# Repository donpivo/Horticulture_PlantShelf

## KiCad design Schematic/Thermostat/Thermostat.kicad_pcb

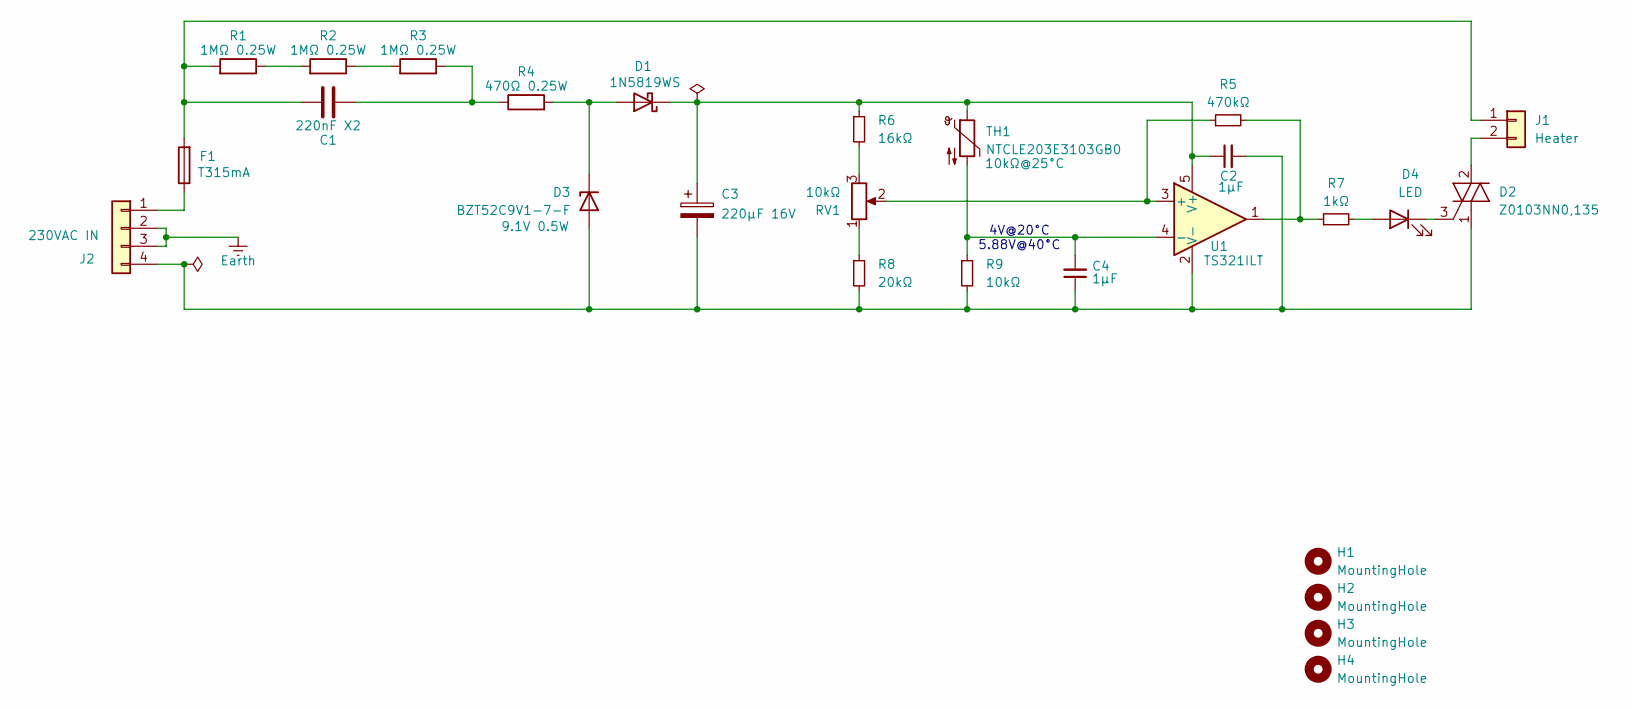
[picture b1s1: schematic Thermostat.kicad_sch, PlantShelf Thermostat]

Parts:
C1: 220nF X2; C_Rect_L18.0mm_W8.0mm_P15.00mm_FKS3_FKP3
C2, C4: 1µF; C_0603_1608Metric_Pad1.08x0.95mm_HandSolder
C3: 220µF 16V; CP_Elec_6.3x7.7
D1: 1N5819WS; D_SOD-123
D2: Z0103NN0,135; SOT-223
D3: BZT52C9V1-7-F; D_SOD-123
D4: LED; LED_D3.0mm_Horizontal_O1.27mm_Z2.0mm
F1: T315mA; Fuse_Littelfuse_372_D8.50mm
H1, H2, H3, H4: MountingHole; MountingHole_3.2mm_M3
J1: Heater; ScrewTerminal_DB128L-5.08-2P-BK-S
J2: 230VAC IN; Pluggable_DB2ERC-5.08-4P-BK
R1, R2, R3: 1MΩ 0.25W; R_1206_3216Metric_Pad1.30x1.75mm_HandSolder
R4: 470Ω 0.25W; R_1206_3216Metric_Pad1.30x1.75mm_HandSolder
R5: 470kΩ; R_0603_1608Metric_Pad0.98x0.95mm_HandSolder
R6: 16kΩ; R_0603_1608Metric_Pad0.98x0.95mm_HandSolder
R7: 1kΩ; R_0603_1608Metric_Pad0.98x0.95mm_HandSolder
R8: 20kΩ; R_0603_1608Metric_Pad0.98x0.95mm_HandSolder
R9: 10kΩ; R_0603_1608Metric_Pad0.98x0.95mm_HandSolder
RV1: 10kΩ; Potentiometer_Bourns_PTV09A-2_Single_Horizontal
TH1: NTCLE203E3103GB0; NTCLE203E3103FB0A
U1: TS321ILT; SOT-23-5

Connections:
Earth: J2.2, J2.3
unnamed: C1.1, R3.1, R4.1
unnamed: D1.2 (A), D3.1 (K), R4.2
unnamed: C2.1, C3.1, D1.1 (K), R6.1, TH1.1, U1.5 (V+)
unnamed: D2.3 (G), D4.1 (K)
unnamed: C2.2, C3.2, C4.1, D2.1 (T1), D3.2 (A), J2.4, R8.2, R9.2, U1.2 (V-)
unnamed: D4.2 (A), R7.2
unnamed: C1.2, F1.2, J1.1, R1.2
unnamed: D2.2 (T2), D2.4 (T2), J1.2
unnamed: F1.1, J2.1
unnamed: R1.1, R2.2
unnamed: R2.1, R3.2
unnamed: R5.2, R7.1, U1.1
unnamed: R6.2, RV1.3
unnamed: R8.1, RV1.1
unnamed: R5.1, RV1.2, U1.3 (+)
unnamed: C4.2, R9.1, TH1.2, U1.4 (-)

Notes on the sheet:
4V@20°C 5.88V@40°C

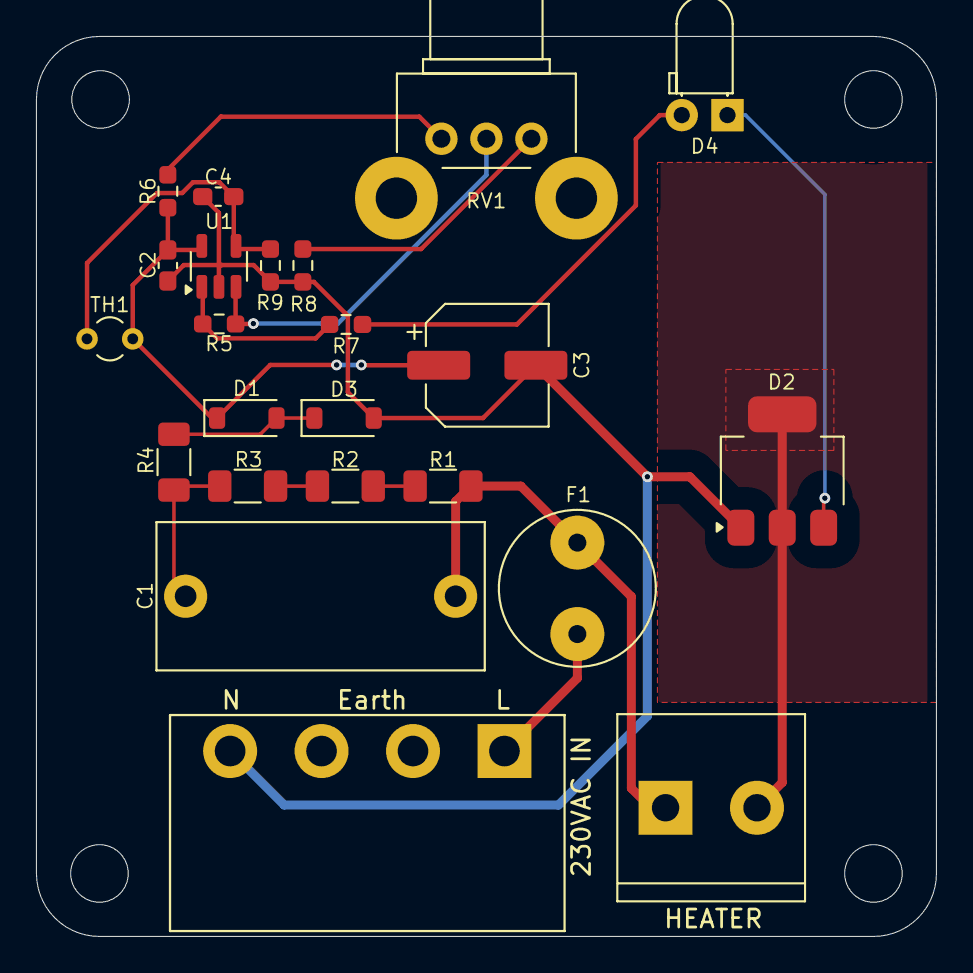
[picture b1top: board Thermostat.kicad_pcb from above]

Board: 2 copper layers, 50.0 x 50.0 mm, 27 parts (0 on the bottom side), 17 nets.

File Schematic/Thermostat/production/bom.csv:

Designator,Footprint,Quantity,Value,LCSC Part #
C1,C_Rect_L18.0mm_W8.0mm_P15.00mm_FKS3_FKP3,1,220nF X2,
"C2, C4",0603,2,1µF,
C3,CP_Elec_6.3x7.7,1,220µF 16V,
D1,D_SOD-123,1,1N5819WS,
D2,SOT-223,1,"Triac_Z0103NN0,135",
D3,D_SOD-123,1,BZT52C9V1-7-F,
D4,LED_D3.0mm_Horizontal_O1.27mm_Z2.0mm,1,LED,
F1,Fuse_Littelfuse_372_D8.50mm,1,T315mA,
J1,ScrewTerminal_DB128L-5.08-2P-BK-S,1,Heater,
J2,Pluggable_DB2ERC-5.08-4P-BK,1,230VAC IN,
"R1, R2, R3",1206,3,1MΩ 0.25W,
R4,1206,1,470Ω 0.25W,
R5,0603,1,1MΩ,
R6,0603,1,27kΩ,
R7,0603,1,1kΩ,
R8,0603,1,47kΩ,
R9,0603,1,10kΩ,
RV1,Potentiometer_Bourns_PTV09A-2_Single_Horizontal,1,20kΩ,
TH1,NTCLE203E3103FB0A,1,NTCLE203E3103GB0,
U1,SOT-23-5,1,TS321ILT,

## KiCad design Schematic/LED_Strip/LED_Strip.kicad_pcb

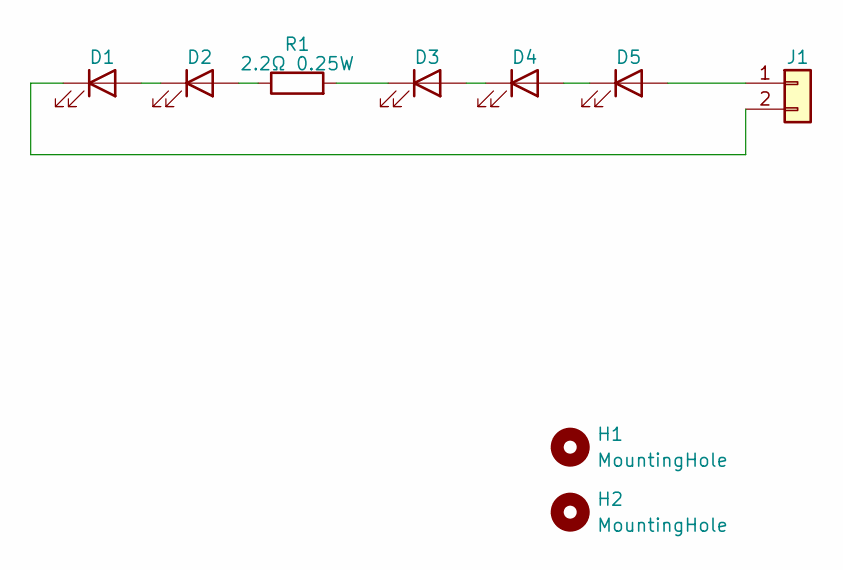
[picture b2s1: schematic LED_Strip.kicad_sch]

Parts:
D1, D2, D3, D4, D5: GW QSLMS2.HM-H8H9-XX52-1U1V; GW_QSLMS2.HM-H8H9-XX53-1U1V
H1, H2: MountingHole; MountingHole_3.2mm_M3
J1: Pads_Dual_3x4
R1: 2.2Ω 0.25W; R_1206_3216Metric_Pad1.30x1.75mm_HandSolder

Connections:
unnamed: D1.2 (A), D2.1 (K)
unnamed: D1.1 (K), J1.2
unnamed: D2.2 (A), R1.1
unnamed: D3.2 (A), D4.1 (K)
unnamed: D3.1 (K), R1.2
unnamed: D4.2 (A), D5.1 (K)
unnamed: D5.2 (A), J1.1

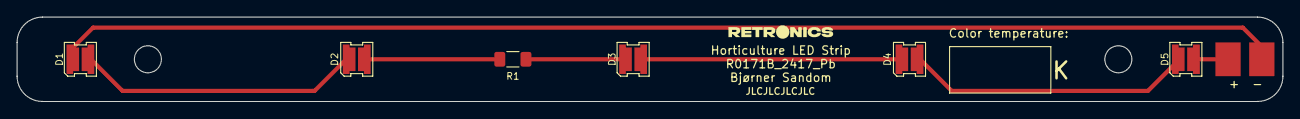
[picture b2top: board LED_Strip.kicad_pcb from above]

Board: 2 copper layers, 150.0 x 10.0 mm, 9 parts (0 on the bottom side), 7 nets.

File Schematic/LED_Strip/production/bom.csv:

Designator,Footprint,Quantity,Value,LCSC Part #
"D1, D2, D3, D4, D5",GW_QSLMS2.HM-H8H9-XX53-1U1V,5,GW QSLMS2.HM-H8H9-XX52-1U1V,
"H1, H2",MountingHole_3.2mm_M3,2,MountingHole,
J1,Pads_Dual_3x4,1,~,
R1,1206,1,2.2Ω 0.25W,

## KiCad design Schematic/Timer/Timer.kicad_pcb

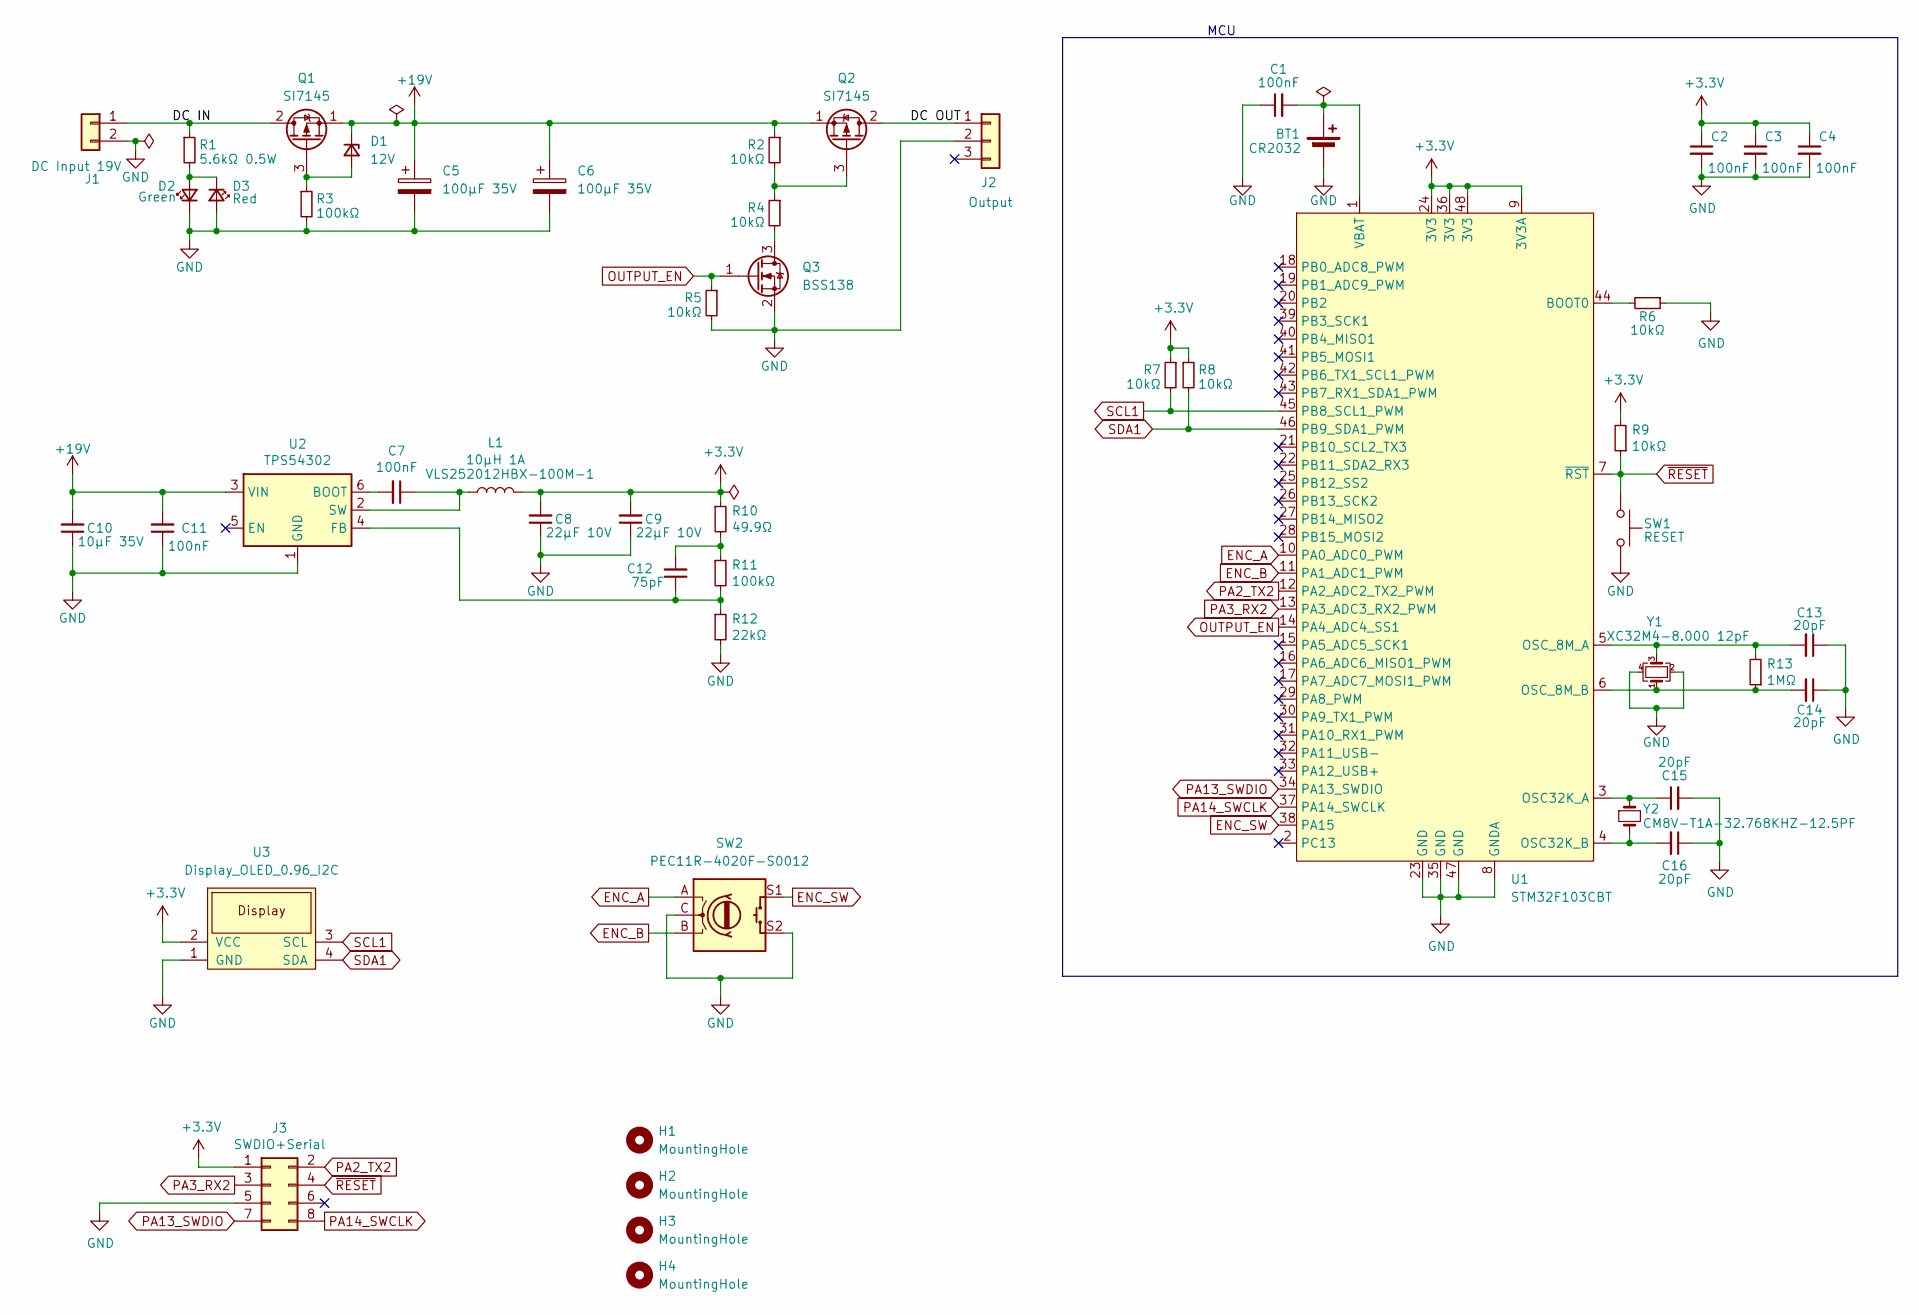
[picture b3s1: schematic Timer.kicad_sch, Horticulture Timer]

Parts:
BT1: CR2032; BS7
C1, C2, C3, C4, C7, C11: 100nF; C_0603_1608Metric_Pad1.08x0.95mm_HandSolder
C5, C6: 100µF 35V; CP_Elec_6.3x7.7
C8, C9: 22µF 10V; C_0603_1608Metric_Pad1.08x0.95mm_HandSolder
C10: 10µF 35V; C_0603_1608Metric_Pad1.08x0.95mm_HandSolder
C12: 75pF; C_0603_1608Metric_Pad1.08x0.95mm_HandSolder
C13, C14, C15, C16: 20pF; C_0603_1608Metric_Pad1.08x0.95mm_HandSolder
D1: 12V; D_SOD-123
D2: Green; LED_0805_2012Metric_Pad1.15x1.40mm_HandSolder
D3: Red; LED_0805_2012Metric_Pad1.15x1.40mm_HandSolder
H1, H2, H3, H4: MountingHole; MountingHole_3.2mm_M3
J1: DC Input 19V; Pluggable_DB2ERC-5.08-2P-BK
J2: Output; Pluggable_DB2ERC-5.08-3P-BK
J3: SWDIO+Serial; IDC-Header_2x04_P2.54mm_Vertical
L1: 10µH 1A; L_Taiyo-Yuden_NR-20xx_HandSoldering
Q1, Q2: SI7145; SON8_SI7135DP-T1-GE3_VIS
Q3: BSS138; SOT-23
R1: 5.6kΩ 0.5W; R_1210_3225Metric_Pad1.30x2.65mm_HandSolder
R2, R4, R5, R6, R7, R8, R9: 10kΩ; R_0603_1608Metric_Pad0.98x0.95mm_HandSolder
R3, R11: 100kΩ; R_0603_1608Metric_Pad0.98x0.95mm_HandSolder
R10: 49.9Ω; R_0603_1608Metric_Pad0.98x0.95mm_HandSolder
R12: 22kΩ; R_0603_1608Metric_Pad0.98x0.95mm_HandSolder
R13: 1MΩ; R_0603_1608Metric_Pad0.98x0.95mm_HandSolder
SW1: RESET; SKTHACE010
SW2: PEC11R-4020F-S0012
U1: STM32F103CBT; LQFP-48_7x7mm_P0.5mm
U2: TPS54302; SOT-23-6_Handsoldering
U3: Display_OLED_0.96_I2C; Display_OLED_0.96in_I2C
Y1: XC32M4-8.000 12pF; Crystal_SMD_3225-4Pin_3.2x2.5mm
Y2: CM8V-T1A-32.768KHZ-12.5PF; Crystal_SMD_MicroCrystal_CC8V-T1A-2Pin_2.0x1.2mm_HandSolder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

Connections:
+3.3V: C2.1, C3.1, C4.1, C8.2, C9.2, J3.1, L1.2, R7.1, R8.1, R9.2, R10.1, U1.9 (3V3A), U1.24 (3V3), U1.36 (3V3), U1.48 (3V3), U3.2 (VCC)
+19V: C5.1, C6.1, C10.2, C11.2, D1.1 (K), Q1.1 (S), Q2.1 (S), R2.1, U2.3 (VIN)
/DC IN: J1.1, Q1.2 (D), R1.1
/DC OUT: J2.1, Q2.2 (D)
ENC_A: SW2.A, U1.10 (PA0_ADC0_PWM)
ENC_B: SW2.B, U1.11 (PA1_ADC1_PWM)
ENC_SW: SW2.S1, U1.38 (PA15)
GND: BT1.2 (-), C1.1, C2.2, C3.2, C4.2, C5.2, C6.2, C8.1, C9.1, C10.1, C11.1, C13.1, C14.1, C15.2, C16.1, D2.1 (K), D3.2 (A), J1.2, J2.2, J3.5, Q3.2 (S), R3.2, R5.2, R6.1, R12.2, SW1.2, SW2.C, SW2.S2, U1.8 (GNDA), U1.23 (GND), U1.35 (GND), U1.47 (GND), U2.1 (GND), U3.1 (GND), Y1.2, Y1.4
unnamed: BT1.1 (+), C1.2, U1.1 (VBAT)
unnamed: C12.2, R10.2, R11.1
unnamed: D1.2 (A), Q1.3 (G), R3.1
unnamed: D2.2 (A), D3.1 (K), R1.2
unnamed: Q2.3 (G), R2.2, R4.1
unnamed: Q3.3 (D), R4.2
unnamed: R6.2, U1.44 (BOOT0)
unnamed: C15.1, U1.3 (OSC32K_A), Y2.1
unnamed: C16.2, U1.4 (OSC32K_B), Y2.2
unnamed: C13.2, R13.2, U1.5 (OSC_8M_A), Y1.3
unnamed: C14.2, R13.1, U1.6 (OSC_8M_B), Y1.1
unnamed: C7.2, U2.6 (BOOT)
unnamed: C12.1, R11.2, R12.1, U2.4 (FB)
unnamed: C7.1, L1.1, U2.2 (SW)
OUTPUT_EN: Q3.1 (G), R5.1, U1.14 (PA4_ADC4_SS1)
PA2_TX2: J3.2, U1.12 (PA2_ADC2_TX2_PWM)
PA3_RX2: J3.3, U1.13 (PA3_ADC3_RX2_PWM)
PA13_SWDIO: J3.7, U1.34 (PA13_SWDIO)
PA14_SWCLK: J3.8, U1.37 (PA14_SWCLK)
SCL1: R7.2, U1.45 (PB8_SCL1_PWM), U3.3 (SCL)
SDA1: R8.2, U1.46 (PB9_SDA1_PWM), U3.4 (SDA)
~RESET: J3.4, R9.1, SW1.1, U1.7 (~RST)

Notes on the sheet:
MCU

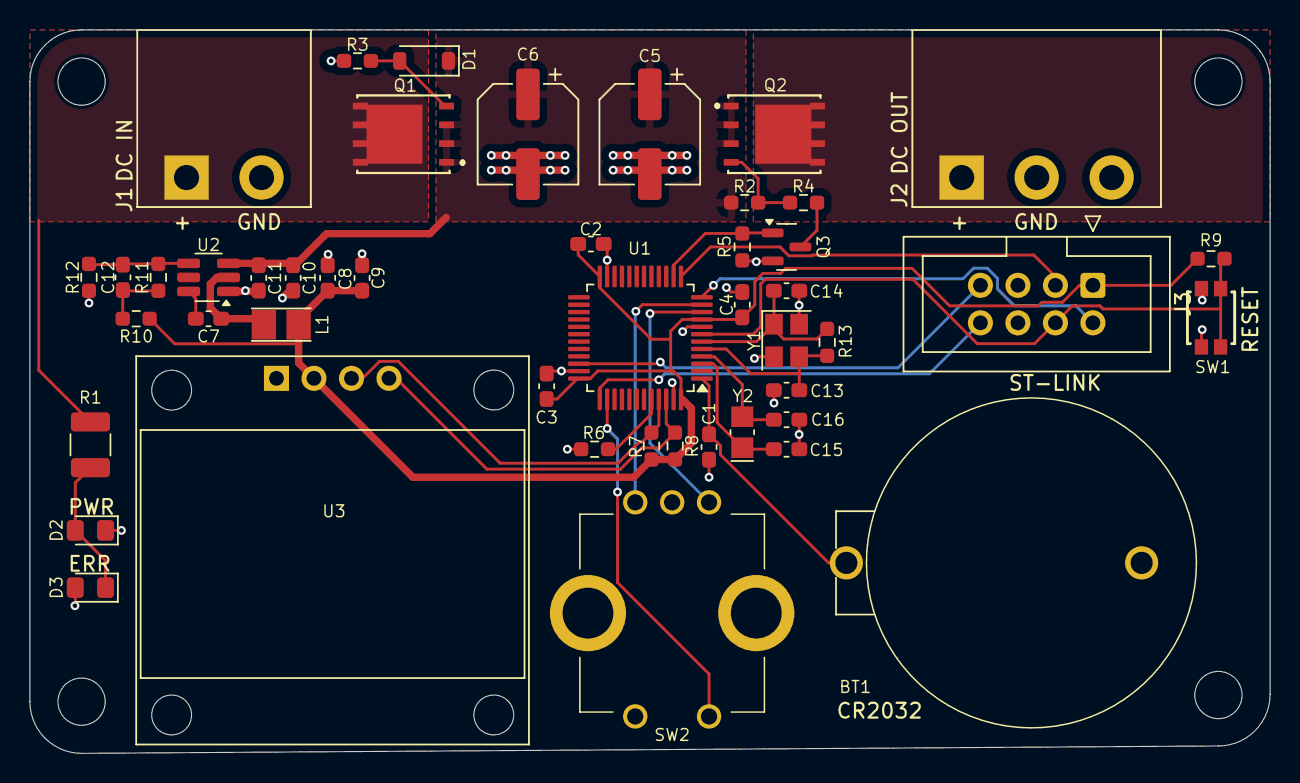
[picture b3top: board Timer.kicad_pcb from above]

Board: 2 copper layers, 84.0 x 49.0 mm, 51 parts (0 on the bottom side), 30 nets.

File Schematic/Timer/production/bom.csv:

Designator,Footprint,Quantity,Value,LCSC Part #
BT1,BS7,1,CR2032,
"C1, C11, C2, C3, C4, C7",0603,6,100nF,
C10,0603,1,10µF 35V,
C12,0603,1,75pF,
"C13, C14, C15, C16",0603,4,20pF,
"C5, C6",CP_Elec_6.3x7.7,2,100µF 35V,
"C8, C9",0603,2,22µF 10V,
D1,D_SOD-123,1,12V,
D2,0805,1,Green,
D3,0805,1,Red,
J1,Pluggable_DB2ERC-5.08-2P-BK,1,DC Input 19V,
J2,Pluggable_DB2ERC-5.08-3P-BK,1,Output,
J3,IDC-Header_2x04_P2.54mm_Vertical,1,SWDIO+Serial,
L1,L_Taiyo-Yuden_NR-20xx_HandSoldering,1,10µH 1A,
"Q1, Q2",SON8_SI7135DP-T1-GE3_VIS,2,SI7145,
Q3,SOT-23,1,BSS138,
R1,1210,1,5.6kΩ 0.5W,
R10,0603,1,49.9Ω,
"R11, R3",0603,2,100kΩ,
R12,0603,1,22kΩ,
R13,0603,1,1MΩ,
"R2, R4, R5, R6, R7, R8, R9",0603,7,10kΩ,
SW1,SKTHACE010,1,RESET,
SW2,PEC11R-4020F-S0012,1,PEC11R-4020F-S0012,
U1,LQFP-48_7x7mm_P0.5mm,1,STM32F103CBT,
U2,SOT-23-6_Handsoldering,1,TPS54302,
U3,Display_OLED_0.96in_I2C,1,Display_OLED_0.96_I2C,
Y1,Crystal_SMD_3225-4Pin_3.2x2.5mm,1,XC32M4-8.000 12pF,
Y2,Crystal_SMD_MicroCrystal_CC8V-T1A-2Pin_2.0x1.2mm_HandSoldering,1,CM8V-T1A-32.768KHZ-12.5PF,

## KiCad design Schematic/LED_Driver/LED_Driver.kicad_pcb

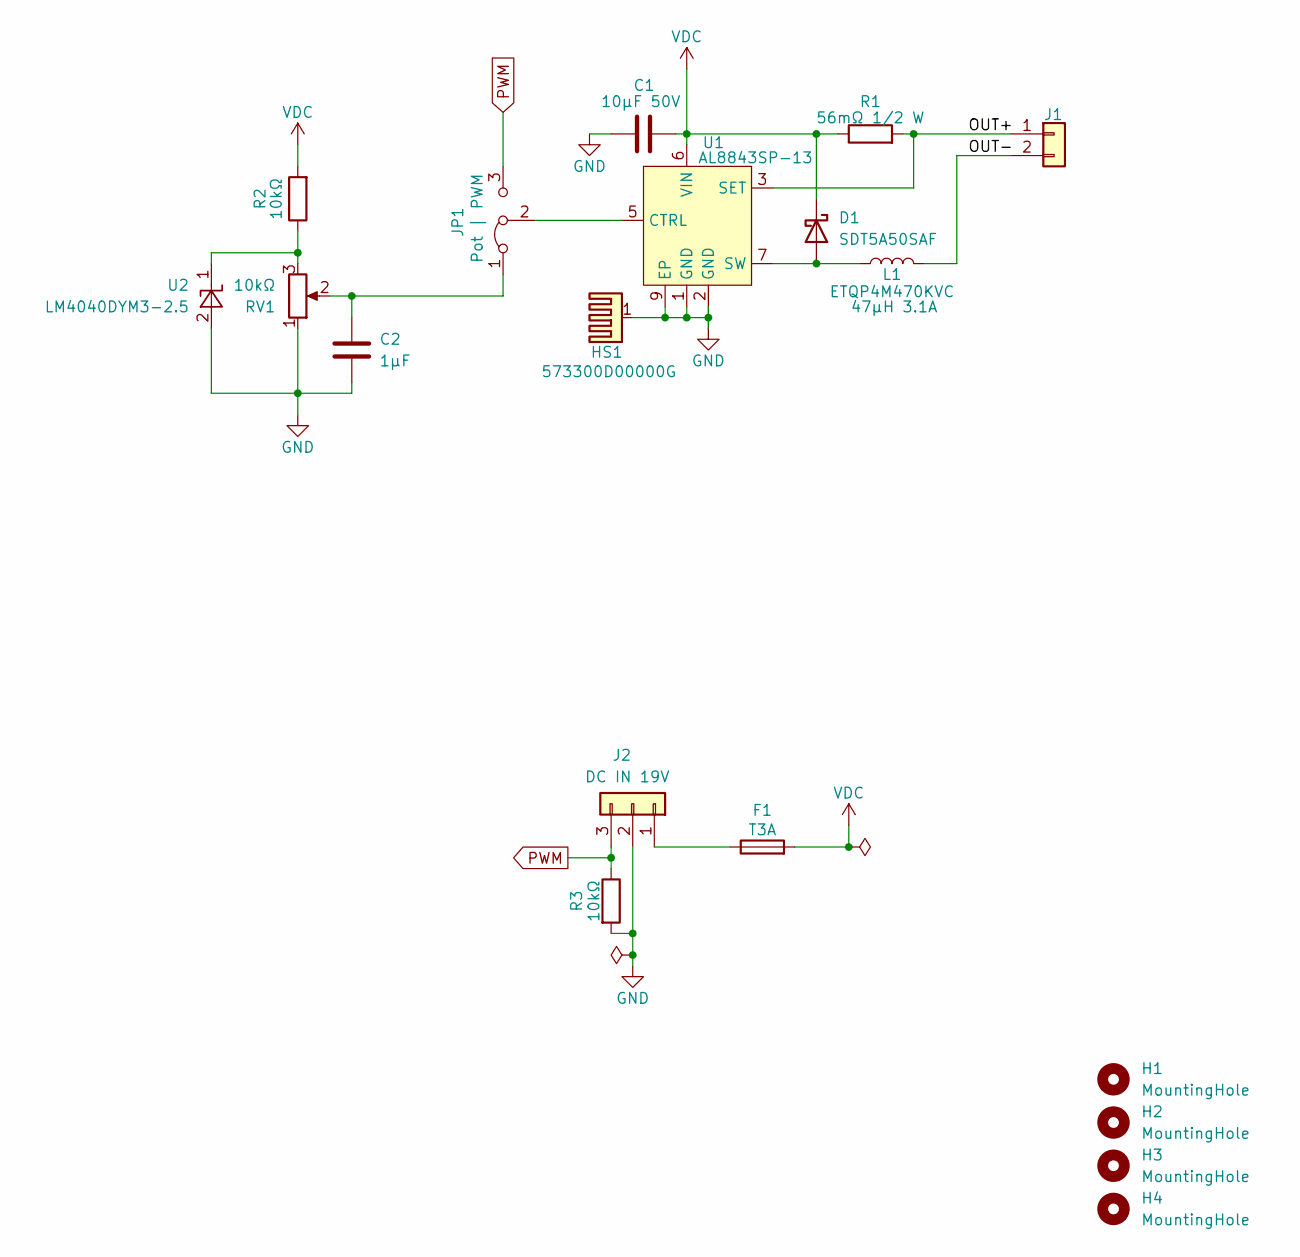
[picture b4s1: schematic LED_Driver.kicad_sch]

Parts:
C1: 10µF 50V; C_0805_2012Metric_Pad1.18x1.45mm_HandSolder
C2: 1µF; R_0805_2012Metric_Pad1.20x1.40mm_HandSolder
D1: SDT5A50SAF; SDT5A50SAF-13
F1: T3A; Fuse_1206_3216Metric_Pad1.42x1.75mm_HandSolder
H1, H2, H3, H4: MountingHole; MountingHole_3.2mm_M3
HS1: 573300D00000G; Heatsink-573300D00000G
J1: Conn_01x02; ScrewTerminal_DB128L-5.08-2P-BK-S
J2: DC IN 19V; Pluggable_DB2ERC-5.08-3P-BK
JP1: Pot | PWM; PinHeader_1x03_P2.54mm_Vertical
L1: ETQP4M470KVC; ETQ-P4M_KVC
R1: 56mΩ 1/2 W; R_1206_3216Metric_Pad1.30x1.75mm_HandSolder
R2, R3: 10kΩ; R_0805_2012Metric_Pad1.20x1.40mm_HandSolder
RV1: 10kΩ; Potentiometer_Bourns_PTV09A-2_Single_Horizontal
U1: AL8843SP-13; SOIC127P600X155-9N
U2: LM4040DYM3-2.5; SOT-23

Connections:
/OUT+: J1.1, R1.2, U1.3 (SET)
/OUT-: J1.2, L1.1
GND: C1.2, C2.2, HS1.1, J2.2, R3.2, RV1.1, U1.1 (GND), U1.2 (GND), U1.9 (EP), U2.2 (A)
unnamed: D1.2 (A), L1.2, U1.7 (SW), U1.8 (SW)
unnamed: F1.1, J2.1
unnamed: C2.1, JP1.1 (A), RV1.2
unnamed: JP1.2 (C), U1.5 (CTRL)
unnamed: R2.1, RV1.3, U2.1 (K)
PWM: J2.3, JP1.3 (B), R3.1
VDC: C1.1, D1.1 (K), F1.2, R1.1, R2.2, U1.6 (VIN)

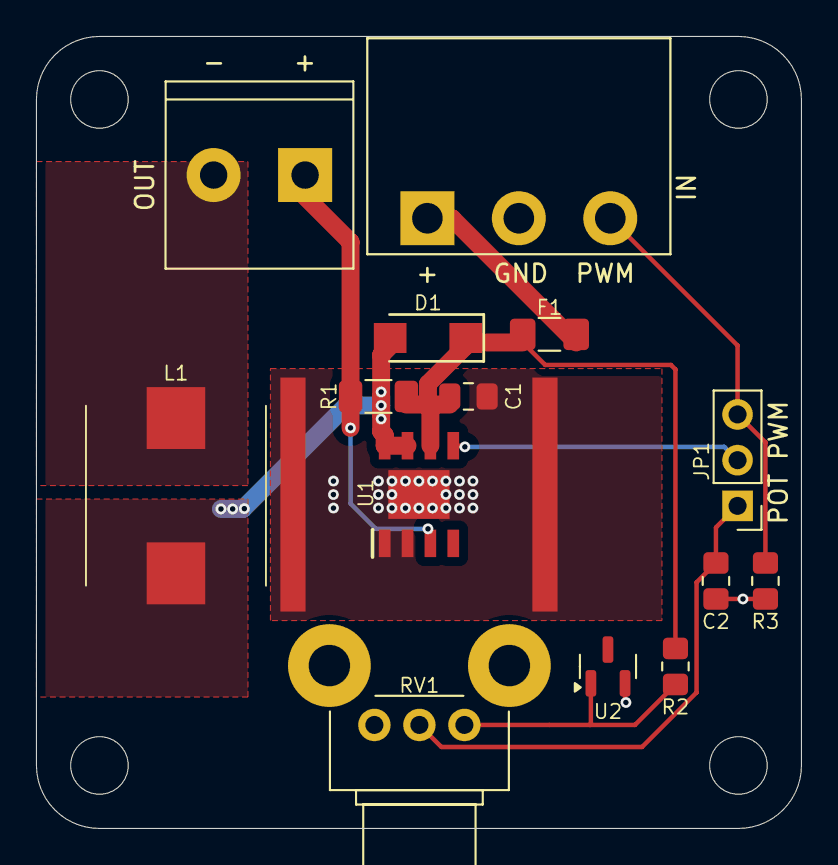
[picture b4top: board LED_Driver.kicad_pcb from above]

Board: 2 copper layers, 42.5 x 44.0 mm, 19 parts (0 on the bottom side), 10 nets.

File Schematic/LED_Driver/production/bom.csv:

Designator,Footprint,Quantity,Value,LCSC Part #
C1,0805,1,10µF 50V,
C2,0805,1,1µF,
D1,SDT5A50SAF-13,1,SDT5A50SAF,
F1,1206,1,T3A,
"H1, H2, H3, H4",MountingHole_3.2mm_M3,4,MountingHole,
HS1,Heatsink-573300D00000G,1,573300D00000G,
J1,ScrewTerminal_DB128L-5.08-2P-BK-S,1,Conn_01x02,
J2,Pluggable_DB2ERC-5.08-3P-BK,1,DC IN 19V,
L1,ETQ-P4M_KVC,1,ETQP4M470KVC,
R1,1206,1,50mΩ,
R2,0805,1,10kΩ,
R3,0805,1,100kΩ,
RV1,Potentiometer_Bourns_PTV09A-2_Single_Horizontal,1,10kΩ,
U1,SOIC127P600X155-9N,1,AL8843SP-13,
U2,SOT-23,1,LM4040DYM3-2.5,

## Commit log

2025-03-31 File cleanup
2025-04-06 Rearranged schematic, added copy ring
